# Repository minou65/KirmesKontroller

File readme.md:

# Kirmes kontroller
- [Kirmes kontroller](#kirmes-kontroller)
	- [Beschreibung](#beschreibung)
		- [Hauptfunktionen](#hauptfunktionen)
		- [Technische Spezifikationen](#technische-spezifikationen)
	- [Anschlüsse](#anschlüsse)
		- [Klemmenblöcke](#klemmenblöcke)
		- [Jumper-Einstellungen](#jumper-einstellungen)
	- [Controller](#controller)
	- [Librarys](#librarys)
	- [Pin mapping](#pin-mapping)
	- [internal pins](#internal-pins)
	- [external pins](#external-pins)
	- [Schema](#schema)
	- [Board](#board)
		- [Notwendige Änderungen auf v1 board](#notwendige-änderungen-auf-v1-board)
	- [Partliste](#partliste)
	- [Audio-Wiedergabe](#audio-wiedergabe)
		- [Unterstützte Audioformate](#unterstützte-audioformate)
		- [SD-Karte Setup](#sd-karte-setup)
		- [Kirmes-Sounds Quellen](#kirmes-sounds-quellen)
		- [Sounddateien bearbeiten](#sounddateien-bearbeiten)
			- [Online-Audio-Editoren](#online-audio-editoren)
			- [Desktop-Software](#desktop-software)
			- [Bearbeitungs-Tipps für Kirmes-Sounds](#bearbeitungs-tipps-für-kirmes-sounds)
			- [Batch-Verarbeitung](#batch-verarbeitung)
	- [Konfiguration](#konfiguration)
		- [System-Konfiguration](#system-konfiguration)
			- [System Configuration](#system-configuration)
			- [Sound Settings](#sound-settings)
			- [ServoOutput Konfiguration](#servooutput-konfiguration)
			- [Output Konfiguration](#output-konfiguration)
			- [Bedienelemente](#bedienelemente)
			- [Navigation](#navigation)
	- [WiFi](#wifi)
		- [Standard-Passwort](#standard-passwort)
		- [Standard-IP-Adresse](#standard-ip-adresse)
		- [OTA (Over-The-Air Updates)](#ota-over-the-air-updates)
		- [Konfigurationsoptionen](#konfigurationsoptionen)
		- [Blinkcodes](#blinkcodes)
	- [Firmware](#firmware)
		- [Firmware-Update über Web-Interface](#firmware-update-über-web-interface)
		- [Firmware-Update über OTA](#firmware-update-über-ota)
	- [Reset](#reset)
		- [Reset-Vorgang](#reset-vorgang)

## Beschreibung

Der KirmesKontroller ist ein vielseitiger NMRA-DCC-Decoder, der speziell für Kirmes- und Karussell-Anwendungen entwickelt wurde. Basierend auf dem leistungsstarken YB-ESP32-S3-AMP Mikrocontroller, bietet er umfangreiche Steuerungs- und Audio-Funktionen.

### Hauptfunktionen

**Ausgänge:**

- 8 digitale Ausgänge für Beleuchtung, Motoren und Effekte
- 3 Servo-Ausgänge für präzise Bewegungssteuerung
- Maximale Belastung: 500mA pro Ausgang

**Eingänge:**

- 2 digitale Eingänge für Taster- und Sensorfunktionen
- Manueller Betrieb unabhängig vom DCC-Signal möglich

**Konnektivität:**

- WiFi-Access-Point für direkten Zugriff
- Integration in bestehende WiFi-Netzwerke
- Web-basierte Konfigurationsoberfläche
- Over-The-Air (OTA) Updates

**Steuerungsmöglichkeiten:**

- **DCC-Kommandos:** Standard NMRA-DCC-Protokoll
- **Web-Interface:** Browserbasierte Steuerung
- **Digitale Eingänge:** Lokale Taster und Sensoren

**Audio-System:**

- Integrierte I2S-Audio-Wiedergabe
- SD-Karten-Unterstützung für Sounddateien
- Vielfältige Audioformate (MP3, WAV, FLAC, etc.)

### Technische Spezifikationen

**Stromversorgung:**

- **DC-Betrieb:** 8-28V Gleichspannung
- **AC-Betrieb:** 18-36V Wechselspannung
- **Ausgangsleistung:** 500mA pro Kanal
- **Wichtiger Hinweis:** Bei Jumper J1 auf Position "5V" darf der Gesamtstrom 1A nicht überschreiten

**Abmessungen und Anschlüsse:**

- Kompakte Bauform für einfache Integration
- Schraubklemmen für sichere Verbindungen
- Status-LEDs für visuelles Feedback

## Anschlüsse

### Klemmenblöcke

| Klemme | Beschreibung | Spezifikation |
|--------|--------------|---------------|
| **X1** | Versorgungsspannung | 8-28V DC / 18-36V AC |
| **X2** | DCC-Signal | NMRA-DCC-Eingang |
| **X3** | Verbraucher (-) | Gemeinsamer Minuspol |
| **X4** | Verbraucher (+) | 5V/12-28V DC (abhängig von J1) |
| **X5-X7** | Servo-Anschlüsse | PWM-Ausgänge für Servos |
| **X8** | Digitale Eingänge | Input 1 und 2 |

### Jumper-Einstellungen

**J1 - Ausgangsspannung:**

- Position "5V": Ausgänge mit 5V (max. 1A Gesamtstrom)
- Position "VIN": Ausgänge mit Eingangsspannung (max. 500mA pro Ausgang)

## Controller

[YB-ESP32-S3-AMP](https://github.com/yellobyte/YB-ESP32-S3-AMP)

## Librarys

- [ESP32-audioI2S](https://github.com/schreibfaul1/ESP32-audioI2S) - Audio-Wiedergabe über I2S
- [IotWebConf](https://github.com/prampec/IotWebConf) - Web-Konfigurationsoberfläche
- [ArduinoOTA](https://github.com/esp8266/Arduino/tree/master/libraries/ArduinoOTA) - Over-The-Air Updates

## Pin mapping

## internal pins

```c++
#define SD_CS         10 
#define SPI_MOSI      11
#define SPI_MISO      13
#define SPI_SCK       12
#define I2S_DOUT       7
#define I2S_BCLK       5
#define I2S_LRCLK      6
#define LED_BUILTIN   47

#define DCC_INPUT     40
#define WIFI_RESET    39

```

## external pins

```c++
static uint8_t ChannelToGPIOMapping[8] = {
	17, // O11
	16, // O12
	15, // O13
	14, // O14
	10, // O15
	9,  // O16
	8,  // O17
	4  // O18
};

static uint8_t ServoChannelToGPIOMapping[3] = {
	2, // O21
	42, // O22
	41 // O23
};

#define INPUT1        21
#define INPUT2        38
```

## Schema

## Board

### Notwendige Änderungen auf v1 board

## Partliste

| Part | Value |
|------|-------|
| B1 | B80R DIO |
| C1 | 2200u 35V |
| C2 | 220u |
| C3 | 100n |
| C4 | 100n |
| C5 | 100n |
| D1 | BAT42 |
| D2 | BAT42 |
| F1 | 900mA |
| IC1 | R-78E05-1.0 |
| IC2 | YB-ESP32-S3-AMP-V2 |
| IC3 | ULN2803 |
| J1 | MPE 087-1-003 |
| LED1 | green 3mm |
| OK1 | 6N137 |
| R1 | 4.7k |
| R2 | 1k5 |
| R3 | 10k |
| R4 | 10k |
| R5 | 10k |
| R6 | 330R |
| R7 | 330R |
| RESET | MPE 087-1-002 |
| X1 | DG240 2,54-2 |
| X2 | DG240 2,54-2 |
| X3 | DG240 2,54-8 |
| X4 | DG240 2,54-8 |
| X5 | 22-23-2031 |
| X6 | 22-23-2031 |
| X7 | 22-23-2031 |
| X8 | 22-23-2031 |

## Audio-Wiedergabe

Der KirmesKontroller unterstützt die Wiedergabe von Sounddateien über das integrierte I2S-Interface. Die Audiodaten werden von einer SD-Karte gelesen und über den angeschlossenen Verstärker ausgegeben.

### Unterstützte Audioformate

| Format | Spezifikation | Bemerkungen |
|--------|---------------|-------------|
| **MP3** | Standard | Vollständig unterstützt |
| **AAC** | Standard | Vollständig unterstützt |
| **AACP** | Mono | Nur Mono-Wiedergabe |
| **WAV** | 8/16 Bit | Bits per Sample: 8 oder 16 |
| **FLAC** | Verlustfrei | Blockgrösse max. 24.576 Bytes |
| **Vorbis** | ≤196 kBit/s | Bitrate-Begrenzung beachten |
| **M4A** | Standard | Vollständig unterstützt |

### SD-Karte Setup

Die Audiodateien müssen auf einer SD-Karte gespeichert werden.

**Empfohlene SD-Karten-Struktur:**

```text
/sounds/
├── ambient/
│   ├── carousel.mp3
│   └── fairground.wav
├── effects/
│   ├── bell.mp3
│   └── whistle.wav
└── music/
    ├── waltz.mp3
    └── polka.mp3
```

### Kirmes-Sounds Quellen

Für authentische Kirmes- und Karussell-Sounds:

- **Pond5:** [Karussell & Kirmes Sounds](https://www.pond5.com/de/search?kw=karussell-unterhaltung-park-kirmes&media=sfx)
- **Freesound.org:** Community-basierte Sammlung von Soundeffekten
- **YouTube Audio Library:** Kostenlose Hintergrundmusik und Effekte

### Sounddateien bearbeiten

Für die optimale Nutzung mit dem KirmesKontroller sollten Audiodateien entsprechend bearbeitet werden. Hier sind einige nützliche Tools und Tipps:

#### Online-Audio-Editoren

**Audio Cutter** - Kostenloser Online-Editor für MP3-Dateien:

- **Features:** Schneiden, Trimmen, Fade-In/Out, Lautstärke anpassen
- **Formate:** MP3, WAV, M4A, FLAC, OGG, AMR, MP4
- **Link:** [Audio Cutter](https://www.audiocutter.org/de/mp3-cutter-online)

**TwistedWave Online** - Erweiterte Audio-Bearbeitung:

- **Features:** Mehrspur-Bearbeitung, Effekte, Normalisierung
- **Formate:** WAV, MP3, AIFF, FLAC, OGG
- **Link:** [TwistedWave](https://twistedwave.com/online/)

#### Desktop-Software

**Audacity** (Kostenlos):

- Professionelle Audio-Bearbeitung
- Unterstützt alle gängigen Formate
- Plugins für Spezialeffekte
- **Download:** [audacityteam.org](https://www.audacityteam.org/)

#### Bearbeitungs-Tipps für Kirmes-Sounds

**Loops erstellen:**

- Nahtlose Wiederholungen für Hintergrundmusik
- Fade-Out am Ende und Fade-In am Anfang vermeiden Knackgeräusche
- Optimale Loop-Länge: 30-120 Sekunden

**Lautstärke normalisieren:**

- Alle Sounds auf einheitliche Lautstärke bringen
- Empfohlener Pegel: -6 dB bis -3 dB
- Vermeidung von Clipping (Übersteuerung)

**Dateioptimierung:**

- **MP3:** 128-320 kBit/s für gute Qualität
- **WAV:** 16 Bit, 44.1 kHz für unkomprimierte Qualität
- **Dateiname:** Kurze, aussagekräftige Namen ohne Sonderzeichen

#### Batch-Verarbeitung

Für grössere Sammlungen:

- **FFmpeg** (Kommandozeilen-Tool) für automatische Konvertierung
- **Audacity** mit Makros für wiederkehrende Bearbeitungen
- **Format Factory** für Windows-Nutzer

## Konfiguration

Die Konfiguration des KirmesKontrollers erfolgt über das Web-Interface, das unter der IP-Adresse des Geräts erreichbar ist. Nach der erfolgreichen Verbindung können Sie auf die Konfigurationsseite zugreifen.

### System-Konfiguration

Die System-Konfiguration ist über `http://[IP-Adresse]/config` erreichbar und bietet folgende Einstellungsmöglichkeiten:

#### System Configuration

**Thing name:**
- Name des KirmesKontrollers (z.B. `kDecoder`)
- Eindeutige Identifikation im Netzwerk

**AP password:**
- Passwort für den Access Point Modus
- Wird verwendet, wenn keine WLAN-Verbindung besteht

**WiFi SSID:**
- Name des WLAN-Netzwerks (z.B. `1000-2575`)
- Netzwerk für die Internetverbindung

**WiFi password:**
- Passwort für das WLAN-Netzwerk

**Startup delay (seconds):**
- Verzögerung beim Start in Sekunden (z.B. `5`)
- Zeit bis zur vollständigen Initialisierung

#### Sound Settings

**Volume:**
- Lautstärke-Einstellung (0-21, z.B. `5`)
- Globale Audio-Lautstärke

**Mono:**
- Mono-Audio-Wiedergabe aktivieren/deaktivieren

**Balance:**
- Stereo-Balance-Einstellung (z.B. `0`)
- Links (16) / Rechts (-16) -Verteilung der Audio-Ausgabe

#### ServoOutput Konfiguration

Für jeden Servo-Ausgang können folgende Parameter konfiguriert werden:

**Designation:**
- Bezeichnung des Servos (z.B. `Karussel`)
- Beschreibender Name für die Identifikation

**Mode:**
- Betriebsmodus (z.B. `Motor (1)`)
- Definiert das Verhalten des Servo-Ausgangs

**DCC Address:**
- DCC-Adresse für die Steuerung (z.B. `3`)
- NMRA-DCC-Protokoll-Adresse

**Start delay (ms):**
- Startverzögerung in Millisekunden (z.B. `130`)
- Verzögerung vor der Aktivierung

**Multiplier:**
- Multiplikator für die Geschwindigkeit (z.B. `20`)
- Faktor zur Geschwindigkeitsanpassung

**Motor Speed:**
- Motorgeschwindigkeit (0-255, z.B. `255`)
- PWM-Wert für die Geschwindigkeit

**Filename:**
- Audio-Datei (z.B. `/carousel-sound-looped.mp3`)
- Sound-Datei von der SD-Karte

**Active Duration (ms):**
- Aktive Dauer in Millisekunden (z.B. `30000`)
- Laufzeit des Effekts

**Input Pin:**
- Zugeordneter Eingang (z.B. `Input1`)
- Digitaler Eingang für manuelle Steuerung

#### Output Konfiguration

Für jeden digitalen Ausgang können folgende Parameter konfiguriert werden:

**Designation:**
- Bezeichnung des Ausgangs (z.B. `Feuer`)
- Beschreibender Name

**Mode:**
- Betriebsmodus (z.B. `Feuer (3)`)
- Spezifischer Effekt-Modus

**DCC Address:**
- DCC-Adresse (z.B. `3`)
- Steuerungsadresse

**Brightness:**
- Helligkeit (0-255, z.B. `255`)
- PWM-Wert für die Helligkeit

**Filename:**
- Audio-Datei (optional)
- Begleitender Sound-Effekt

**Active Duration (ms):**
- Aktive Dauer (z.B. `1000`)
- Laufzeit des Effekts

**Input Pin:**
- Zugeordneter Eingang (z.B. `-` für nicht zugeordnet)
- Manuelle Steuerung

#### Bedienelemente

**+ ServoOutput:**
- Neuen Servo-Ausgang hinzufügen

**+ Output:**
- Neuen digitalen Ausgang hinzufügen

**Remove this set:**
- Konfiguration löschen

**Apply:**
- Einstellungen speichern und anwenden

#### Navigation

**Home:**
- Zur Hauptseite zurückkehren

**Reset:**
- System zurücksetzen

**Firmware update:**
- Firmware-Update durchführen

## WiFi

### Standard-Passwort

Wenn nicht mit einem AP verbunden, ist das Standardpasswort `123456789`

### Standard-IP-Adresse

Wenn nicht mit einem AP verbunden, ist die IP-Adresse `192.168.4.1`

### OTA (Over-The-Air Updates)

OTA ist aktiviert und kann verwendet werden. Damit ist es möglich, die Software des KirmesKontrollers zu updaten ohne unter die Anlage kriechen zu müssen. Die IP-Adresse ist entweder die Standard-IP-Adresse oder die vom AP zugewiesene. Port ist Standard.

### Konfigurationsoptionen

Nach dem ersten Start müssen einige Werte eingerichtet werden:

| Parameter | Beschreibung |
|-----------|--------------|
| **Thing name** | Name des Decoders. Es sollten keine Sonderzeichen und Umlaute verwendet werden. Punkte und Leerzeichen sollten ebenfalls nicht verwendet werden. |
| **AP password** | Dieses Passwort wird verwendet, wenn Sie später auf das Gerät zugreifen möchten. Sie müssen ein Passwort mit mindestens 8, höchstens 32 Zeichen verwenden. Es steht Ihnen frei, beliebige Zeichen zu verwenden. Es sollte ein Passwort mit mindestens 12 Zeichen Länge gewählt werden. |
| **WiFi SSID** | Name des WLAN mit welchem der KirmesKontroller verwendet werden soll. |
| **WiFi password** | Das Passwort zum Netzwerk, mit welchem der KirmesKontroller verbunden werden soll. |

### Blinkcodes

Die nachfolgende Tabelle fasst die verschiedenen Blinkcodes der Status-LED zusammen:

| Blinkcode | Bedeutung |
|-----------|-----------|
| **Rasches Blinken** | Meistens ein, unterbrochen durch kurze Aus-Perioden. Eigener AP ist aktiviert und Sie können mit dem Smartphone oder einem Computer eine Verbindung zum KirmesKontroller herstellen. |
| **Wechselblinken** | Der KirmesKontroller versucht mit einem AP zu verbinden. |
| **Langsames Blinken** | Meistens aus mit kurzem Blinken. Der KirmesKontroller ist online und mit dem WLAN verbunden. |

## Firmware

Hier kann, eine entsprechende Datei vorausgesetzt, die Firmware des KirmesKontrollers aktualisiert werden.

### Firmware-Update über Web-Interface

1. Navigieren Sie zur Web-Oberfläche des KirmesKontrollers
2. Wählen Sie die entsprechende Firmware-Datei (*.bin)
3. Starten Sie den Upload-Vorgang
4. Warten Sie, bis der Update-Prozess abgeschlossen ist
5. Das Gerät startet automatisch neu

### Firmware-Update über OTA

- Verwenden Sie die Arduino IDE oder PlatformIO
- Verbinden Sie sich mit der IP-Adresse des KirmesKontrollers
- Laden Sie die neue Firmware direkt hoch

## Reset

Wurde das Passwort vergessen oder funktioniert der KirmesKontroller nicht mehr, kann durch Schliessen des Jumpers RESET während dem Booten der Decoder auf die Werkseinstellungen zurückgesetzt werden.

### Reset-Vorgang

1. **Gerät ausschalten**
2. **RESET-Jumper schliessen** (siehe Platine)
3. **Gerät einschalten** und 10 Sekunden warten
4. **RESET-Jumper öffnen**
5. **Gerät neu starten**

Nach dem Reset sind folgende Standardwerte aktiv:

- **WiFi-Modus:** Access Point
- **SSID:** KirmesKontroller-[MAC]
- **Passwort:** 123456789
- **IP-Adresse:** 192.168.4.1
- **Alle Konfigurationen:** Zurückgesetzt

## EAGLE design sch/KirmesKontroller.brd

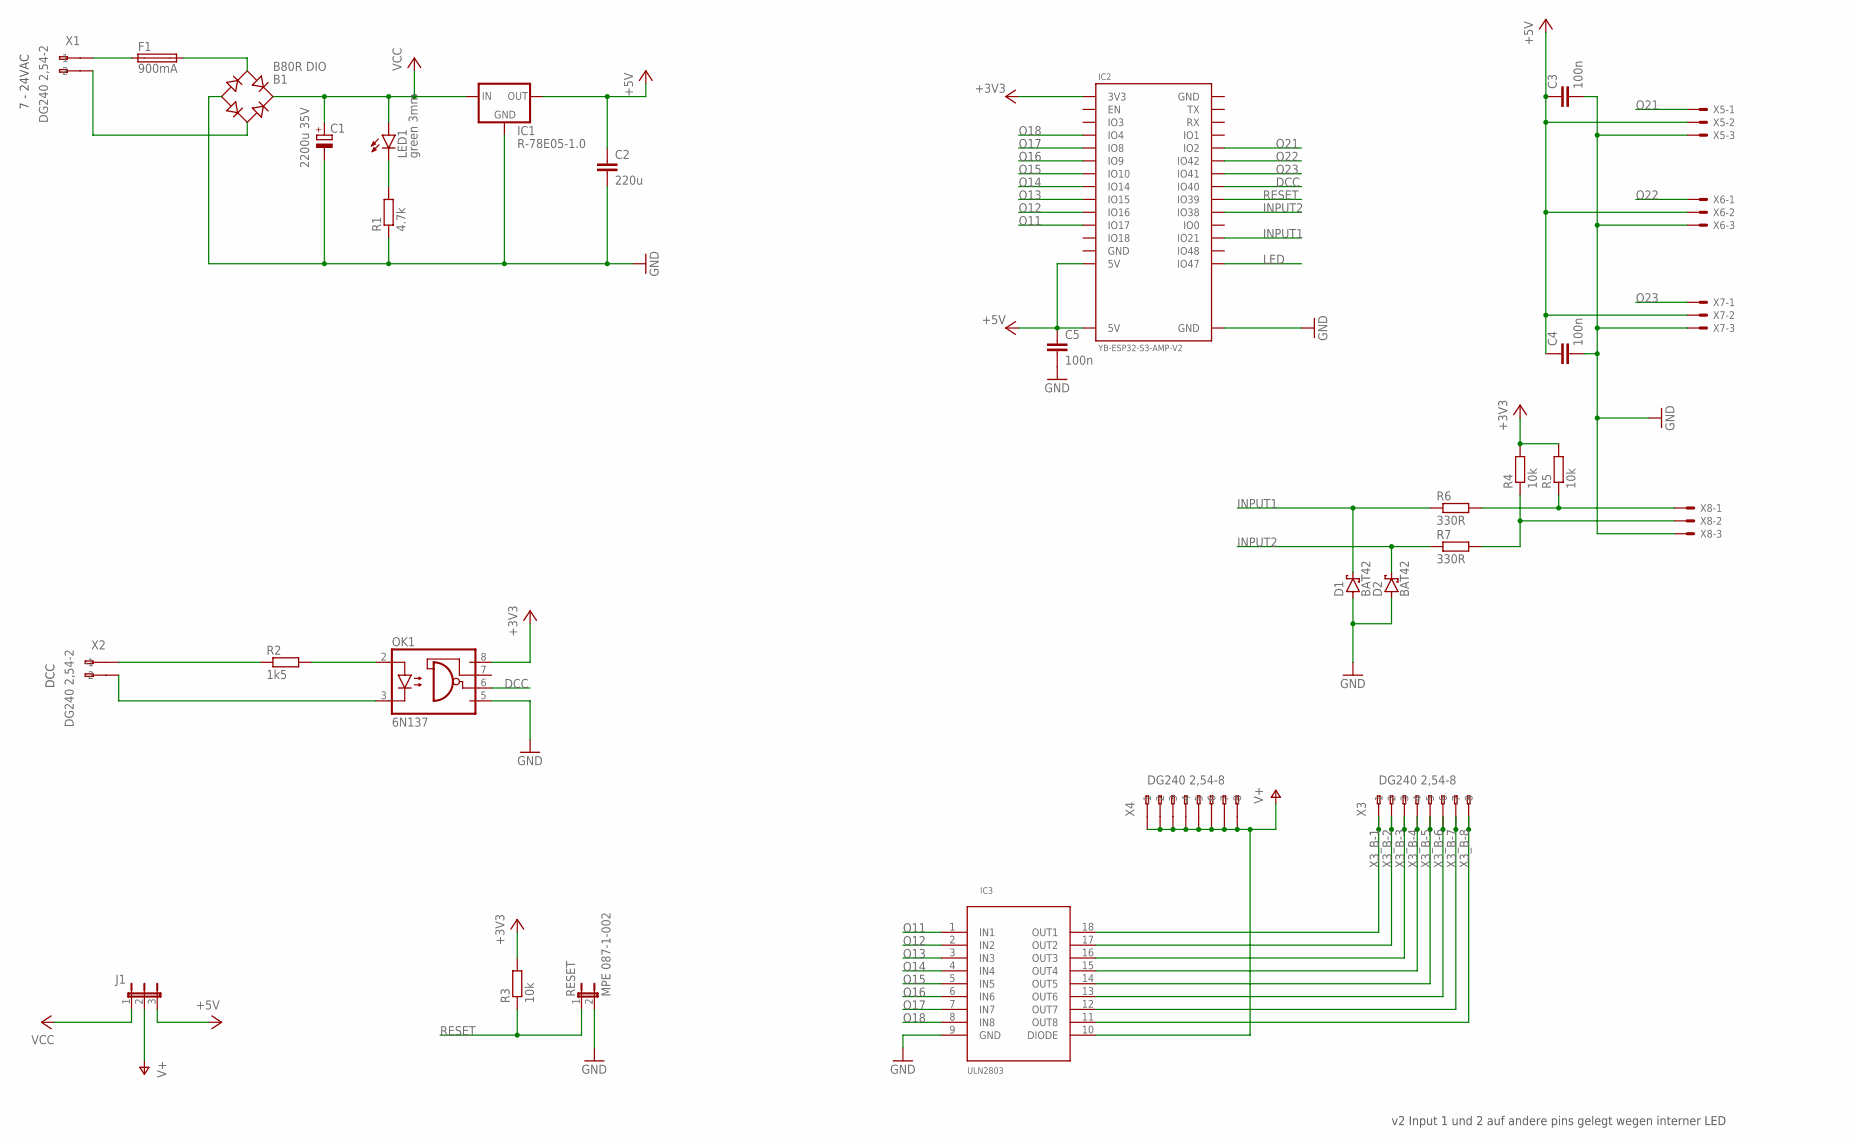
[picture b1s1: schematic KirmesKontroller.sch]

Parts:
B1: B80R DIO; RB1A
C1: 2200u 35V; E5-8,5
C2: 220u; C050-024X044
C3, C4, C5: 100n; C050-024X044
D1, D2: BAT42; DO35-10
F1: 900mA; TE5
IC1: R-78E05-1.0; R-78E-XX1.0
IC2: YB-ESP32-S3-AMP-V2; YB-ESP32-S3-AMP
IC3: ULN2803; DIL18
J1: MPE 087-1-003; JP2
LED1: green 3mm; LED3MM
OK1: 6N137; DIL08
R1: 4.7k; 0207/10
R2: 1k5; 0207/10
R3, R4, R5: 10k; 0207/10
R6, R7: 330R; 0207/10
RESET: MPE 087-1-002; JP1
X1, X2: DG240 2,54-2; 233-202
X3, X4: DG240 2,54-8; 233-508
X5, X6, X7, X8: 22-23-2031

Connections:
+3V3: IC2.3V3, OK1.8 (VCC), R3.2, R4.2, R5.2
+5V: C2.1, C3.1, C4.1, C5.1, IC1.OUT, IC2.5V, IC2.5V@1 (5V), J1.3, X5.2, X6.2, X7.2
DCC: IC2.40 (IO40), OK1.6 (VO)
GND: B1.-, C1.-, C2.2, C3.2, C4.2, C5.2, D1.A, D2.A, IC1.GND, IC2.GND, IC2.GND@1 (GND), IC2.GND@2 (GND), IC3.9 (GND), OK1.5 (GND), R1.1, RESET.2, X5.3, X6.3, X7.3, X8.3
INPUT1: D1.C, IC2.21 (IO21), R6.1
INPUT2: D2.C, IC2.38 (IO38), R7.1
LED: IC2.47 (IO47)
unnamed: R5.1, R6.2, X8.1
unnamed: R4.1, R7.2, X8.2
unnamed: LED1.K (C), R1.2
unnamed: B1.AC1, F1.2
unnamed: B1.AC2, X1.A2 (-2)
unnamed: R2.1, X2.A1 (-1)
unnamed: OK1.2 (A), R2.2
unnamed: OK1.3 (C), X2.A2 (-2)
unnamed: F1.1, X1.A1 (-1)
O11: IC2.17 (IO17), IC3.1 (IN1)
O12: IC2.16 (IO16), IC3.2 (IN2)
O13: IC2.15 (IO15), IC3.3 (IN3)
O14: IC2.14 (IO14), IC3.4 (IN4)
O15: IC2.10 (IO10), IC3.5 (IN5)
O16: IC2.9 (IO9), IC3.6 (IN6)
O17: IC2.8 (IO8), IC3.7 (IN7)
O18: IC2.4 (IO4), IC3.8 (IN8)
O21: IC2.2 (IO2), X5.1
O22: IC2.42 (IO42), X6.1
O23: IC2.41 (IO41), X7.1
RESET: IC2.39 (IO39), R3.1, RESET.1
V+: IC3.10 (DIODE), J1.2, X4.A1 (-1), X4.A2 (-2), X4.A3 (-3), X4.A4 (-4), X4.A5 (-5), X4.A6 (-6), X4.A7 (-7), X4.A8 (-8)
VCC: B1.+, C1.+, IC1.IN, J1.1, LED1.A
X3_B-1: IC3.18 (OUT1), X3.A1 (-1), X3.B1 (B-1)
X3_B-2: IC3.17 (OUT2), X3.A2 (-2), X3.B2 (B-2)
X3_B-3: IC3.16 (OUT3), X3.A3 (-3), X3.B3 (B-3)
X3_B-4: IC3.15 (OUT4), X3.A4 (-4), X3.B4 (B-4)
X3_B-5: IC3.14 (OUT5), X3.A5 (-5), X3.B5 (B-5)
X3_B-6: IC3.13 (OUT6), X3.A6 (-6), X3.B6 (B-6)
X3_B-7: IC3.12 (OUT7), X3.A7 (-7), X3.B7 (B-7)
X3_B-8: IC3.11 (OUT8), X3.A8 (-8), X3.B8 (B-8)

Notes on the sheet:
7 - 24VAC
DCC
v2 Input 1 und 2 auf andere pins gelegt wegen interner LED

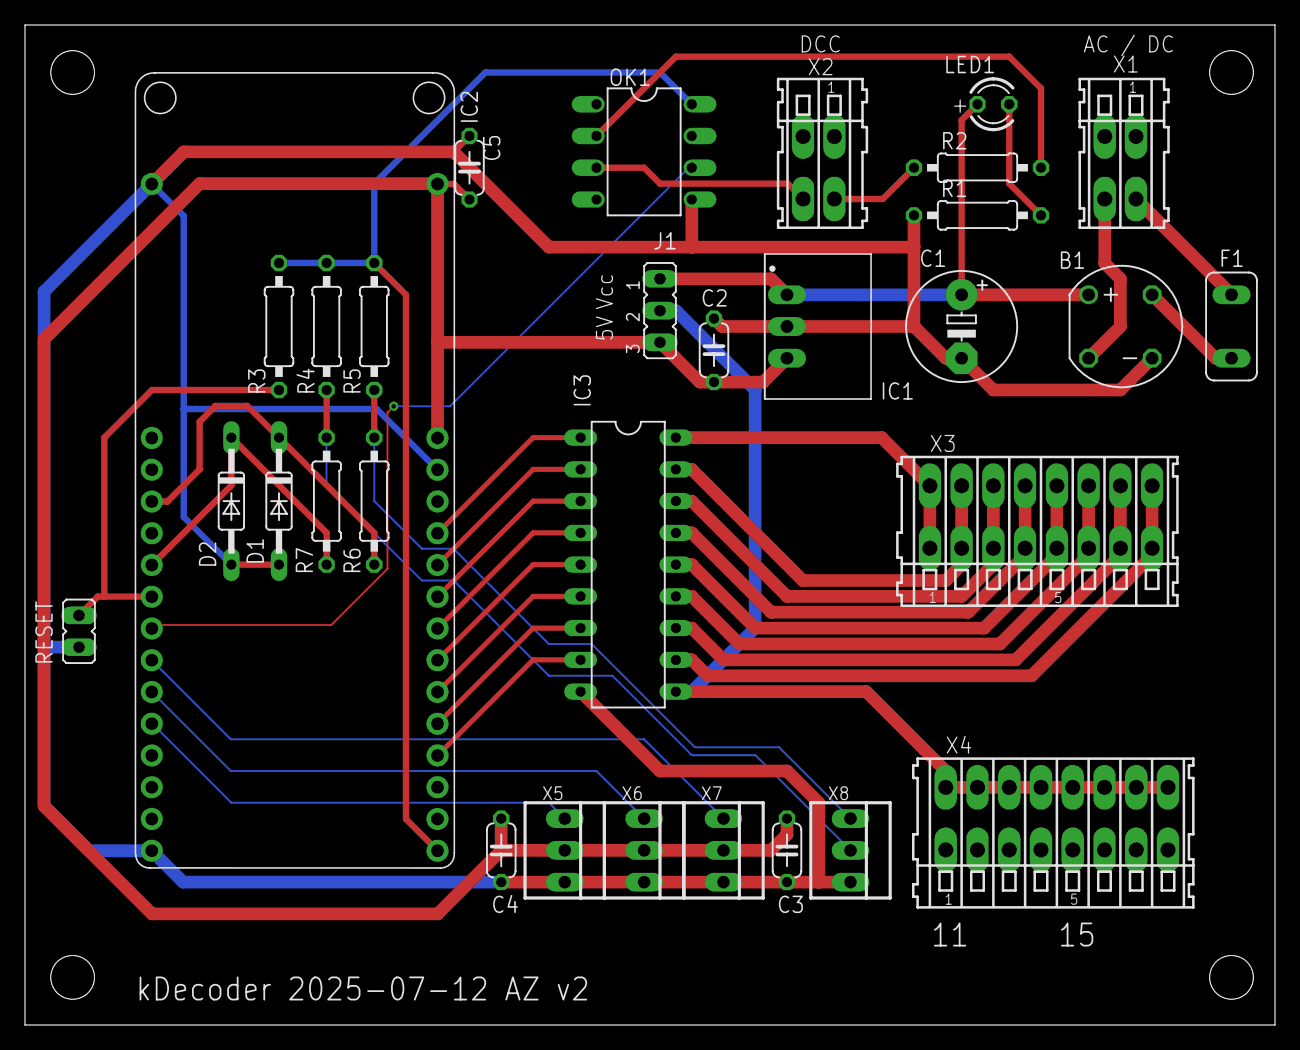
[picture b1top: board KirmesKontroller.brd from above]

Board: 2 copper layers, 100.0 x 80.0 mm, 31 parts (0 on the bottom side), 37 nets.

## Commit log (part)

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2025-07-05 Update readme.md to include detailed pin mapping and controller information
2025-07-05 initial version
2025-07-05 fix.: format change for better reading
2025-07-05 fix: indexes changed
2025-07-05 refactor: remove unused includes and definitions
2025-07-05 feat: add LEDControl classes for LED management and control
2025-07-05 feat: add common header file with decoder mode definitions and configurations
2025-07-05 feat: add MotorControl classes for motor management and control
2025-07-05 refactor: remove MotorControl class and its associated header file
2025-07-05 feat: add SoundControl classes for audio management and control
2025-07-06 initial upload
2025-07-06 fix: exluded *.job files
2025-07-06 fix: update GPIO channel mapping and definitions in pinmapping.h
2025-07-10 Version 1.0
2025-07-10 docs: add schema and board images to README
2025-07-10 fix: add Thumbs.db to .gitignore
2025-07-10 fix: update LED controlapi for esp 3.x
2025-07-10 refactor: improve Motor class implementation and add PWM frequency handling
2025-07-10 refactor: reorganize includes and improve decoder initialization logic
2025-07-12 fixed pinmapping
2025-07-12 feat: add HTML, CSS, and JavaScript for form handling and UI components
2025-07-12 fix: correct INPUT1 and INPUT2 pin definitions in pinmapping.h
2025-07-12 feat: implement web handling functionality with HTML and server setup
2025-07-12 feat: enhance decoder group handling and web integration
2025-07-12 fix: update parameter ranges and defaults for volume, balance, and number of outputs
2025-07-12 feat: implement sound playback functionality with volume and balance controls
2025-07-12 fix: correct sound setup function name and restore sound playback logic
2025-07-12 feat: add Blinker and LED control classes with various modes and functionalities
2025-07-12 fix: update extern variable naming conventions for consistency
2025-07-12 feat: enhance decoder initialization with accessory configuration and support for various modes
2025-07-12 feat: add sound settings initialization in decoder setup
2025-07-12 feat: add SoundSettings struct and methods for sound configuration in accessories class
2025-07-12 feat: enhance Motor class methods to ensure accessory state management during on/off and process operations
2025-07-12 feat: initialize _Input and _sound in accessories constructor for improved state management
2025-07-12 feat: add _Input member variable to accessories class for improved state management
2025-07-12 feat: add Neotimer and input handling methods to accessories class for enhanced functionality
2025-07-12 feat: optimize sound playback logic in loop function for improved performance
2025-07-13 feat: removed not supportet decoder modes
2025-07-13 feat: fix initialization of Mode and correct logical condition in process method
2025-07-13 fix: update parameter access in kDecoderReset and kDecoderInit for consistency
2025-07-13 moved file to subfolder
2025-07-13 feat: override virtual methods in Blinker and derived classes for consistency
2025-07-13 feat: override methods in Motor class for consistency with base class
2025-07-13 refactor: streamline logging in audio callback functions for clarity
2025-07-13 fix: correct formatting and spacing in README for improved readability
2025-07-13 fix: update NUMBER_LEN definition and add input pin values and names
2025-07-13 feat: enhance process and timer management in accessories class with detailed logging
2025-07-13 feat: add Input Pin parameter to SoundGroup class for enhanced configuration
2025-07-13 fix: simplify ON_LEVEL definition for consistent behavior across ESP32
2025-07-13 feat: enhance sound playback logging in accessories class
2025-07-13 fix: correct boundary check in DecoderGroupIsActive and streamline kDecoderInit logic
2025-07-13 fix: update pin mapping for consistency and clarity
2025-07-13 fix: add brightness label to hideClass function for improved UI clarity
2025-07-13 feat: streamline decoder reset logic and enhance task handling in setup
2025-07-13 fix: update InputPinValues to use STR macro for improved clarity and maintainability
2025-07-13 fix: enhance input processing logic in accessories class for better state management
2025-07-14 fix: update volume and balance parameters to specify valid ranges for improved validation
2025-07-14 feat: initial version calss diagram
2025-07-14 fix: add process and on method overrides in various classes for improved functionality
2025-07-14 feat: implement NMRA handling functions and factory default reset logic
2025-07-14 fix: correct size of ChannelToGPIOMapping array to match defined GPIO channels
2025-07-14 feat: enhance NMRA handling with notification functions and setup integration
2025-07-14 fix: comment out debug print statements in audio_info and audio_id3data functions
2025-07-14 pin 47 named
2025-07-14 refactor: optimize sound filename handling and remove unnecessary string usage
2025-07-14 feat: enhance sound playback by setting volume, balance, and mono settings
2025-07-14 fix: update SoundSettings and Accessory class to use uint16_t for volume and timeActive for better type consistency
2025-07-14 fix: uncomment kDecoderInit call in setup for decoder initialization
2025-07-14 docs: update audio format details and add audio editing tools section in README
2025-07-14 fix: remove unused variable declarations in html.h for cleaner code
2025-07-14 fix: add newline for better readability in Accessory::on method
2025-07-14 fix: improve file existence check and error handling in playSound function
2025-07-14 feat: enhance Motor accessory initialization with time-based activation
2025-07-15 feat: add filename validation functions and integrate with form validation
2025-07-15 fix: execute filename validation logic only when group is active
2025-07-16 feat: added ESPServo and ServoControl classes for servo management
2025-07-16 feat: add file extension validation to formValidator function
2025-07-16 feat: implement filename validation in formValidator function
2025-07-17 feat: refactor ServoGroup and OutputGroup to AccessoryGroup and enhance parameter handling
2025-07-17 feat: add partlist file with component details for KirmesKontroller
2025-07-18 feat: add ServoModeValues and ServoModeNames for servo control functionality
2025-07-18 feat: add Mode parameter to ServoGroup for enhanced control options
2025-07-18 chore: update VERSION_MINOR to 7 for the next release
2025-07-18 feat: enable ServoGroup parameters in web configuration setup
2025-07-18 feat: update ServoModeNames to replace 'Zyklus' with 'Pendel' for clarity
2025-07-18 feat: reorder ServoGroup parameter additions in setupWeb for improved clarity
2025-07-18 feat: add ServoModes header file with accessory classes for servo control
2025-07-18 feat: add additional accessory types for enhanced functionality
2025-07-19 refactor: file renamed
2025-07-19 feat: update ServoModeValues to include new range for servo control
2025-07-19 refactor: reorganize SoundGroup parameters and add TimeOn/TimeOff functionality
2025-07-19 feat: add servo group initialization with timeOn and timeOff parameters
2025-07-19 feat: add TimeOn and TimeOff parameters with associated getter methods
2025-07-19 refactor: replace direct member access with getter methods in kDecoderInit for OutputGroup
2025-07-19 feat: add SOUND_FEATURE and NPUT_PIN_FEATURE selecting
2025-07-20 refactor: update ChannelToGPIOMapping size and add ServoChannelToGPIOMapping
2025-07-20 refactor: update ServoModeNames values to match corresponding modes
2025-07-20 refactor: standardize member variable naming
2025-07-20 refactor: improve servo mode handling in kDecoderInit
2025-07-21 refactor: switched to new, external library
2025-07-21 refactor: update ServoControl to use new ESP32Servo and improve interval handling
2025-07-21 fix: fixed typo
2025-07-21 refactor: update kDecoderInit to improve servo handling and preserve values
2025-07-23 feat: add ServoBounce class for enhanced servo bouncing functionality
2025-07-23 feat: add repeatdone method and enhance timer reset functionality
2025-07-23 chore: update version to 0.9.0.236 with new build date and time
2025-07-23 refactor: improve ServoControl class by standardizing method names and enhancing flag handling
2025-07-23 refactor: remove unused variables from ServoControl class
2025-07-23 fix: correct variable name typos and improve logging in ServoControl class
2025-07-23 fix: correct typos in variable names related to target position in ServoControl class
2025-07-24 refactor: clean up process method in ServoBounce class by removing commented-out code
2025-07-24 fix: update servo initialization constants and enhance ServoBounce constructor with additional flags
2025-07-24 refactor: improve code structure and readability in ServoControl class
2025-07-24 fix: enhance initialization logging in ServoControl constructor for better debugging
2025-07-24 fix: correct channel variable in kDecoderInit function for proper servo setup
2025-07-24 feat: update version to 0.9.0.259 with new build date and time
2025-07-24 fix: streamline index increment logic in handleData function
2025-07-24 fix: comment out debug logging in handleData function for cleaner output
2025-07-24 fix: change Serial.print to Serial.println
2025-07-25 fix: change Serial.print to Serial.println for setInputPin and setTimer methods
2025-07-25 fix: reorder initialization of limits and interval time in ServoControl constructor
2025-07-25 fix: ensure proper destruction and processing in ServoAccessory and ServoPendelAccessory classes
2025-07-25 fix: add sound settings handling in kDecoderInit function
2025-07-25 refactor: move Motor class implementation to separate Motorhandling files
2025-07-25 fix: update button behavior and styling in handleRoot function
2025-07-25 fix: reorder include statements for consistency and clarity
2025-07-25 fix: adjust input handling in Accessory class and update pin mode configuration
2025-07-25 fix: simplify MoveServo method and add getServoTenthsPosition for servo position retrieval
2025-07-26 fix: reorganize LED class member variables for improved clarity and structure
2025-07-26 fix: enhance LED class with attach/detach methods and streamline write logic
2025-07-26 fix: update Accessory class for improved input handling and configuration
2025-07-26 fix: update Ausgang and Blinker classes to improve process and state management
2025-07-26 fix: make accessories destructor virtual for proper cleanup in derived classes
2025-07-26 fix: add debug logs in destructors for LED and LEDFader classes
2025-07-26 fix: make destructors virtual in LED, LEDFader, Natrium, and Neon classes for proper cleanup
2025-07-26 fix: refactor LED and LEDFader constructors to use 'pin' parameter and improve PWM channel management
2025-07-26 fix: rename ChannelToGPIOMapping and ServoChannelToGPIOMapping for clarity and consistency
2025-07-26 fix: update constructor parameters in Ausgang and Blinker classes for consistency and clarity
2025-07-26 feat: add PWMChannelManager class for managing PWM channels
2025-07-26 feat: ESP32PWM for LED controlling and proper channel management
2025-07-26 fix: refactor kDecoderInit for improved clarity and consistency in channel management
2025-07-26 refactor: remove PWMChannelManager class and its implementation files
2025-07-27 fix: update visibility arrays to include additional values for timeon and multiplier
2025-07-27 fix: uncomment output mode values and names for proper functionality
2025-07-27 feat: add AusgangDelay class for delayed output handling
2025-07-27 fix: update getNumber method to handle specific cases and improve output parameter naming
2025-07-27 fix: clean up destructor implementations and improve memory management in various classes
2025-07-27 fix: enhance form validation and output handling in web handling module
2025-07-27 fix: add support for new accessory types in decoder initialization
